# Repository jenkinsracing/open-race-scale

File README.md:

# open-race-scale
### Open Source Racecar Scale  
Four load cell scale controller for weighing cars using HX711 load cell module and Raspberry Pi platform. User interface will be via Bluetooth and smart phone app. The overall cost target goal for a complete car weighing system is under $230, at least 75% cheaper than commerically available car scales.
  
### Roadmap  
* Prototype electrical design as Raspberry Pi 3 Hat -> in progress  
* Create simple mechanical design for load cells -> in progress  
* Create Android/iOS app that will connect to the Rasberry Pi 3 to reccive live scale data (via bluetooth)  
* Add advanced features for storing weights for comparision  
* Add option of LCD screen directly on the Raspberry Pi 3  
* Get feedback and feature requests  
  
### Design

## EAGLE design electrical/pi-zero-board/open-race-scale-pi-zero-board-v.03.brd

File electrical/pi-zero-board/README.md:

### Open Race Scale Pi Zero based control board

***THIS BOARD IS NOT YET VALIDATED***

This is an early release version of the integrated control board.  It is not yet ready for production.  It has passed Eagle ERC and DRC for Seeed Fusion PCB.

Forked from https://github.com/jenkinsracing/open-race-scale by Andrew Jenkins no license listed

Uses Pi Zero and integrated HX711 amps instead of Pi 3 and HX711 carrier
boards.

HX711 circuit from Sparkfun Load Cell Amplifier https://github.com/sparkfun/HX711-Load-Cell-Amplifier/tree/V_1.1 license public domain/OSHW

Original designs from Roaddog Labs Ltd are released per the Open Source
Hardware Association guidelines for open source hardware at
http://www.oshwa.org/definition/.

Material specific to the components and documentation that is not
derived from other sources are released under the Creative Commons
Attribution 4.0 International license.

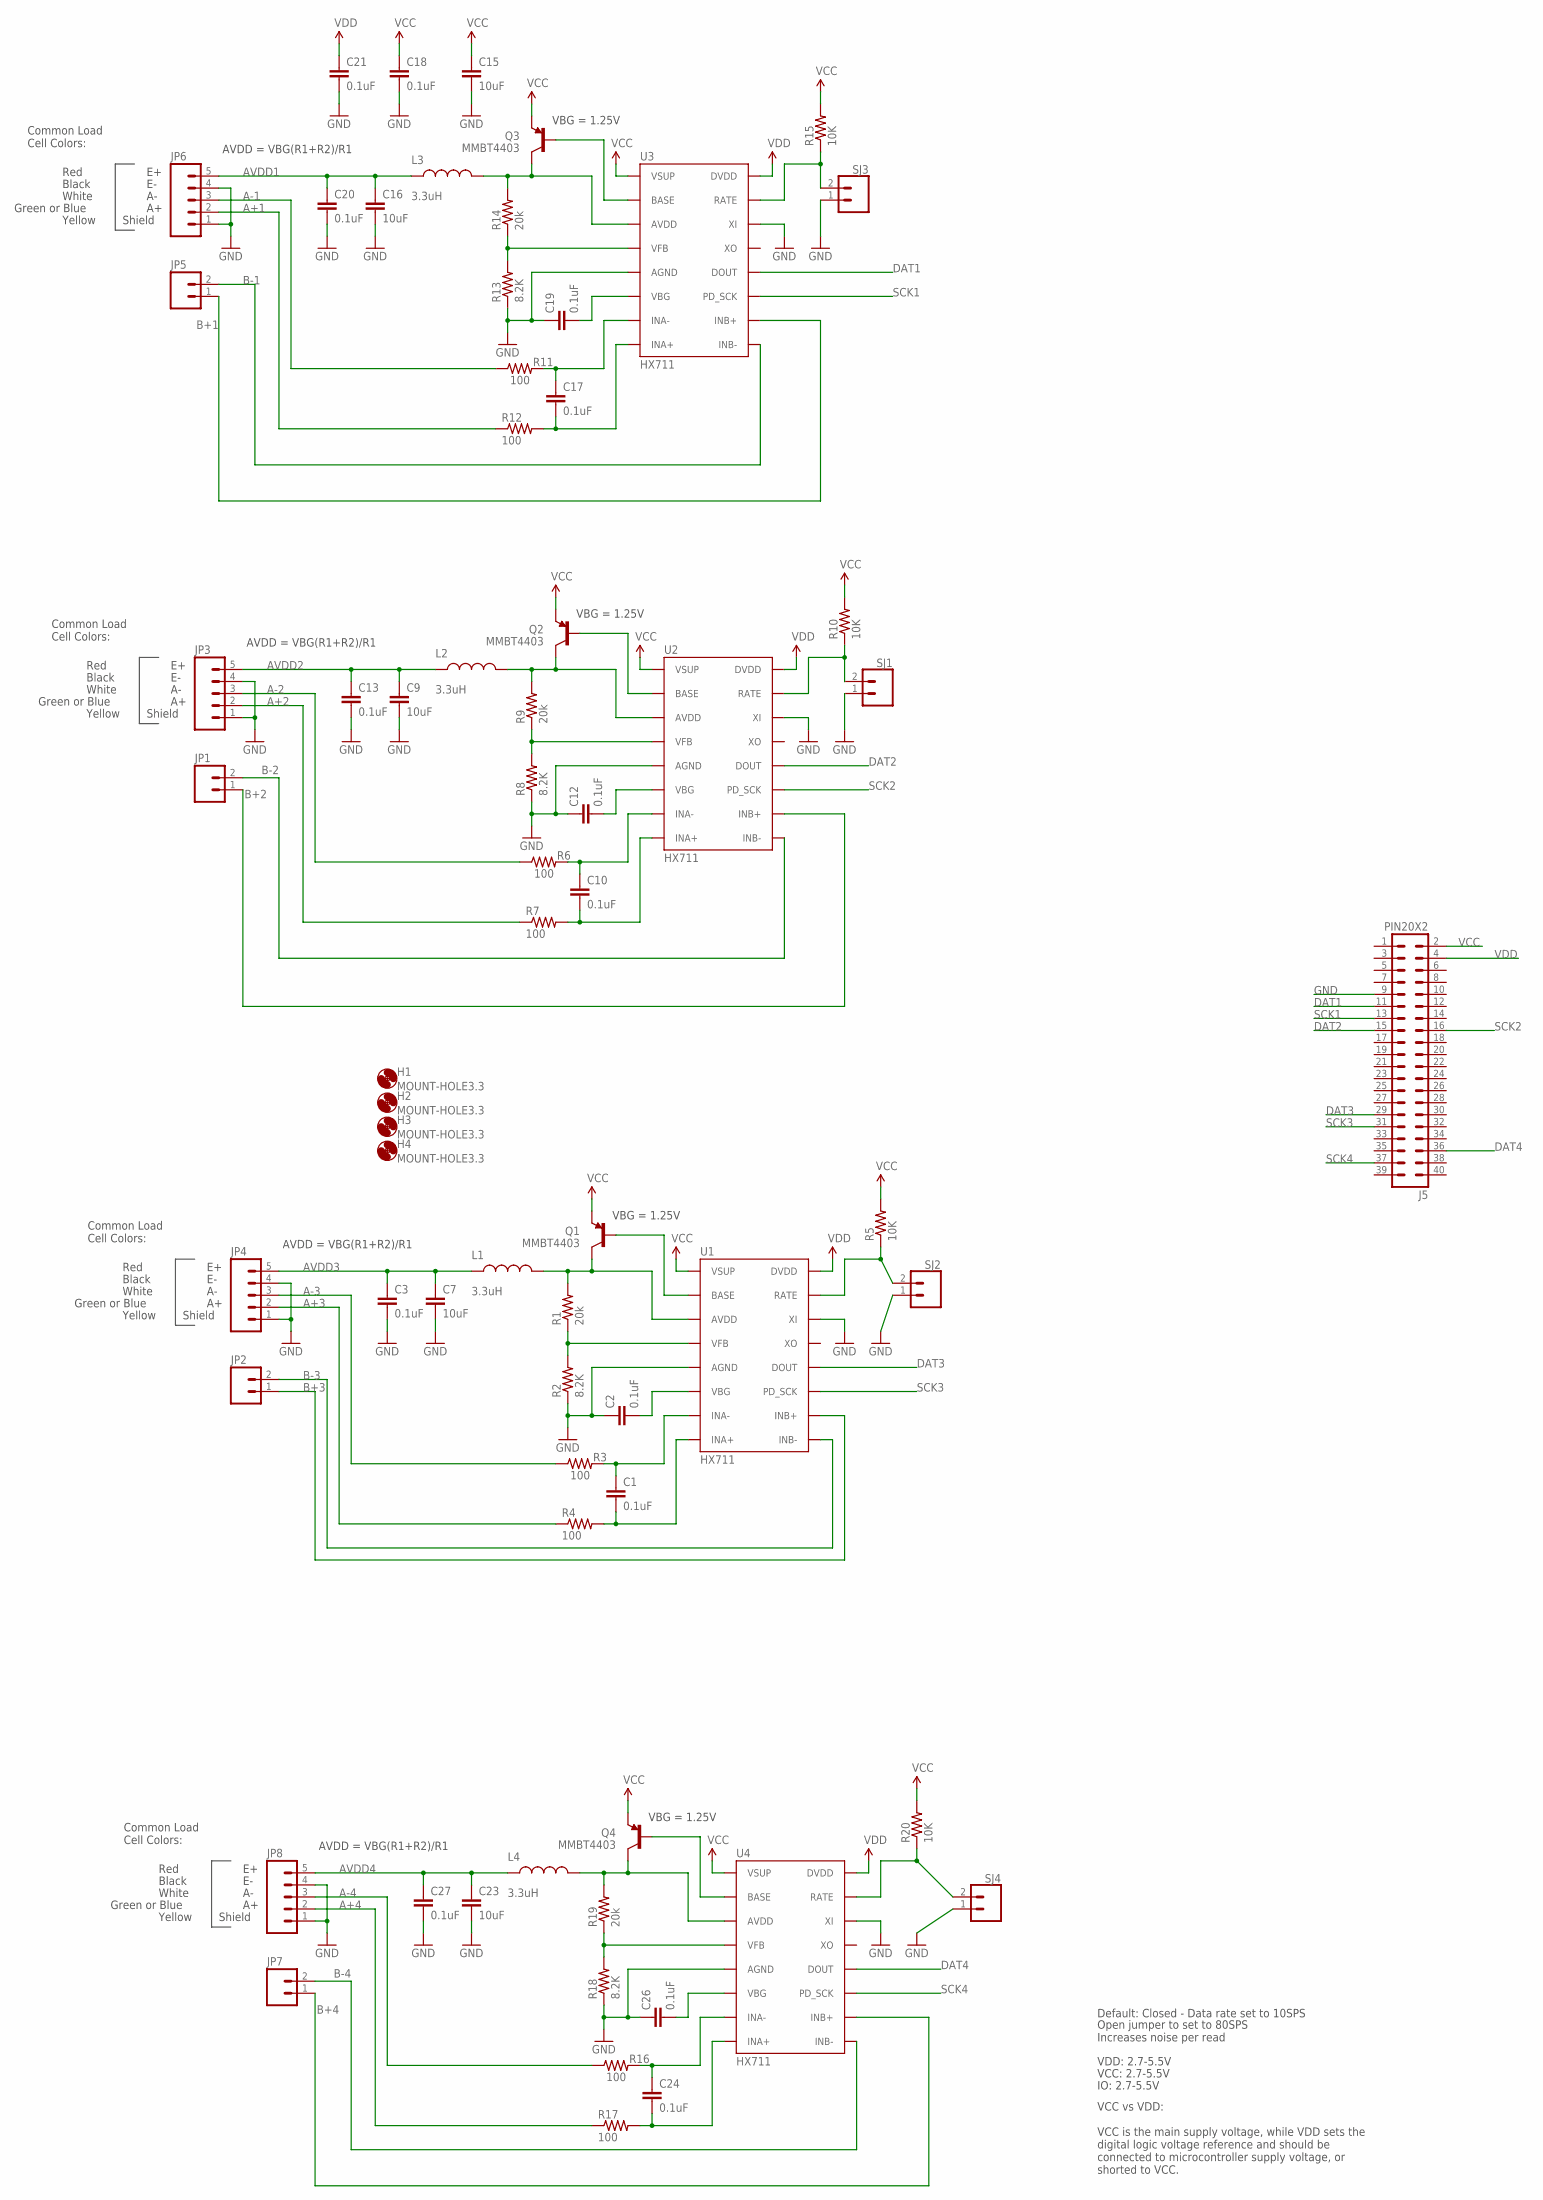
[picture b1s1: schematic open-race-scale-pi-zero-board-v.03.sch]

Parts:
C1, C2, C3, C10, C12, C13, C17, C18, C19, C20, C21, C24, C26, C27: 0.1uF; 0603-CAP
C7, C9, C15, C16, C23: 10uF; 1210
H1, H2, H3, H4: MOUNT-HOLE3.3; 3,3
J5: PIN20X2; PIN_20X2
JP1, JP2, JP5, JP7: M02PTH; 1X02@1
JP3, JP4, JP6, JP8: M05PTH; 1X05
L1, L2, L3, L4: 3.3uH; 0805
Q1, Q2, Q3, Q4: MMBT4403; SOT23-3
R1, R9, R14, R19: 20k; 0603-RES
R2, R8, R13, R18: 8.2K; 0603-RES
R3, R4, R6, R7, R11, R12, R16, R17: 100; 0603-RES
R5, R10, R15, R20: 10K; 0603-RES
SJ1, SJ2, SJ3, SJ4: CONN_02; 1X02
U1, U2, U3, U4: HX711; SO16

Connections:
A+1: JP6.2, R12.1
A+2: JP3.2, R7.1
A+3: JP4.2, R4.1
A+4: JP8.2, R17.1
A-1: JP6.3, R11.1
A-2: JP3.3, R6.1
A-3: JP4.3, R3.1
A-4: JP8.3, R16.1
AVDD1: C16.1, C20.1, JP6.5, L3.1
AVDD2: C9.1, C13.1, JP3.5, L2.1
AVDD3: C3.1, C7.1, JP4.5, L1.1
AVDD4: C23.1, C27.1, JP8.5, L4.1
B+1: JP5.1, U3.10 (INB+)
B+2: JP1.1, U2.10 (INB+)
B+3: JP2.1, U1.10 (INB+)
B+4: JP7.1, U4.10 (INB+)
B-1: JP5.2, U3.9 (INB-)
B-2: JP1.2, U2.9 (INB-)
B-3: JP2.2, U1.9 (INB-)
B-4: JP7.2, U4.9 (INB-)
DAT1: J5.11, U3.12 (DOUT)
DAT2: J5.15, U2.12 (DOUT)
DAT3: J5.29, U1.12 (DOUT)
DAT4: J5.36, U4.12 (DOUT)
GND: C2.1, C3.2, C7.2, C9.2, C12.1, C13.2, C15.2, C16.2, C18.2, C19.1, C20.2, C21.2, C23.2, C26.1, C27.2, J5.9, JP3.1, JP3.4, JP4.1, JP4.4, JP6.1, JP6.4, JP8.1, JP8.4, R2.1, R8.1, R13.1, R18.1, SJ1.1, SJ2.1, SJ3.1, SJ4.1, U1.5 (AGND), U1.14 (XI), U2.5 (AGND), U2.14 (XI), U3.5 (AGND), U3.14 (XI), U4.5 (AGND), U4.14 (XI)
unnamed: R5.1, SJ2.2, U1.15 (RATE)
unnamed: C1.1, R3.2, U1.7 (INA-)
unnamed: C1.2, R4.2, U1.8 (INA+)
unnamed: Q1.1 (B), U1.2 (BASE)
unnamed: L1.2, Q1.3 (C), R1.2, U1.3 (AVDD)
unnamed: R1.1, R2.2, U1.4 (VFB)
unnamed: C2.2, U1.6 (VBG)
unnamed: R8.2, R9.1, U2.4 (VFB)
unnamed: C12.2, U2.6 (VBG)
unnamed: C17.1, R11.2, U3.7 (INA-)
unnamed: C17.2, R12.2, U3.8 (INA+)
unnamed: Q4.1 (B), U4.2 (BASE)
unnamed: R18.2, R19.1, U4.4 (VFB)
unnamed: C26.2, U4.6 (VBG)
unnamed: L4.2, Q4.3 (C), R19.2, U4.3 (AVDD)
unnamed: R20.1, SJ4.2, U4.15 (RATE)
unnamed: C24.1, R16.2, U4.7 (INA-)
unnamed: C24.2, R17.2, U4.8 (INA+)
unnamed: Q2.1 (B), U2.2 (BASE)
unnamed: L2.2, Q2.3 (C), R9.2, U2.3 (AVDD)
unnamed: R10.1, SJ1.2, U2.15 (RATE)
unnamed: C10.1, R6.2, U2.7 (INA-)
unnamed: C10.2, R7.2, U2.8 (INA+)
unnamed: Q3.1 (B), U3.2 (BASE)
unnamed: R13.2, R14.1, U3.4 (VFB)
unnamed: C19.2, U3.6 (VBG)
unnamed: L3.2, Q3.3 (C), R14.2, U3.3 (AVDD)
unnamed: R15.1, SJ3.2, U3.15 (RATE)
SCK1: J5.13, U3.11 (PD_SCK)
SCK2: J5.16, U2.11 (PD_SCK)
SCK3: J5.31, U1.11 (PD_SCK)
SCK4: J5.37, U4.11 (PD_SCK)
VCC: C15.1, C18.1, J5.2, Q1.2 (E), Q2.2 (E), Q3.2 (E), Q4.2 (E), R5.2, R10.2, R15.2, R20.2, U1.1 (VSUP), U2.1 (VSUP), U3.1 (VSUP), U4.1 (VSUP)
VDD: C21.1, J5.4, U1.16 (DVDD), U2.16 (DVDD), U3.16 (DVDD), U4.16 (DVDD)

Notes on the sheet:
VBG = 1.25V
AVDD = VBG(R1+R2)/R1
Red
Black
White
Green or Blue
Common Load Cell Colors:
Shield
Yellow
VCC: 2.7-5.5V
Default: Closed - Data rate set to 10SPS
Open jumper to set to 80SPS Increases noise per read
IO: 2.7-5.5V
VDD: 2.7-5.5V
VCC vs VDD: VCC is the main supply voltage, while VDD sets the digital logic voltage reference and should be connected to microcontroller supply voltage, or shorted to VCC.

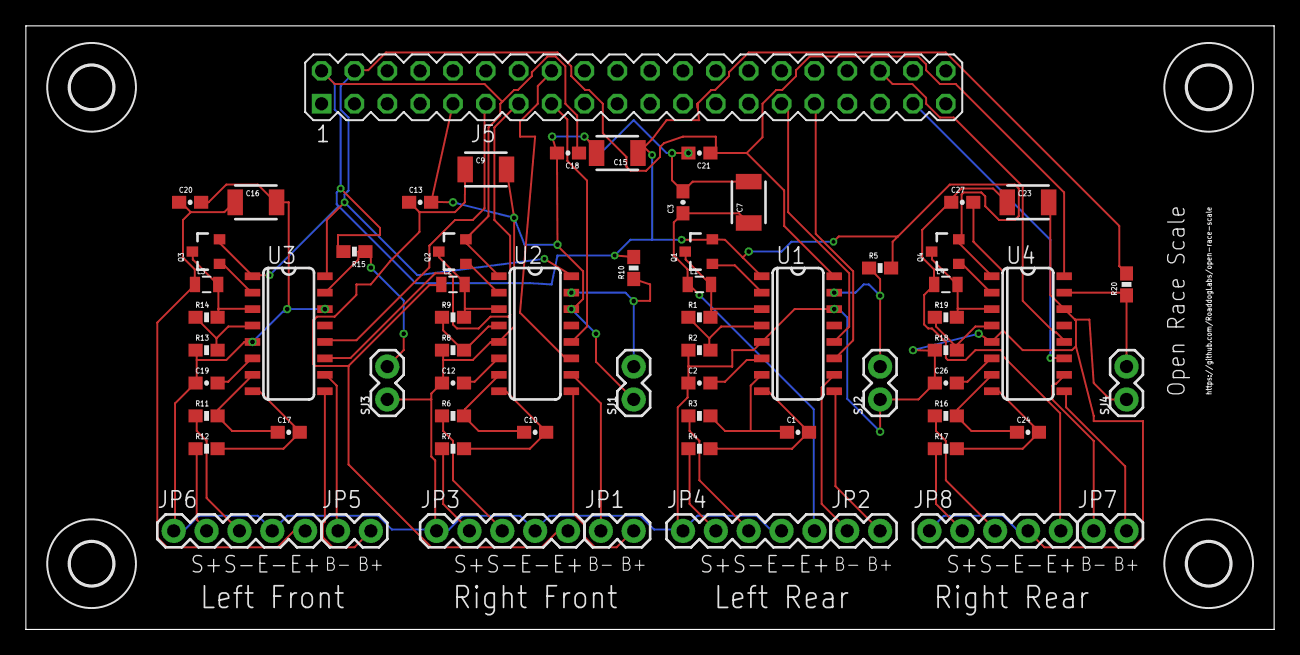
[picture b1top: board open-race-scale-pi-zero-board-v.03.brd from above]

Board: 2 copper layers, 96.5 x 46.7 mm, 68 parts (0 on the bottom side), 59 nets.

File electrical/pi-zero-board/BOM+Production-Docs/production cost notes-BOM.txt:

BOM for open race scale pi zero board with and without carriers

Partlist exported from /Users/dave/Documents/SparkFun_HX711_Load_Cell_v11/SparkFun_HX711_Load_Cell_v11.sch at 6/15/17 5:34 PM

Part      Value                      Device                     Package                           Description                          PROD_ID     VALUE   
4xC1        0.1uF                      0.1UF-25V-5%(0603)         0603-CAP                          CAP-08604                            CAP-08604   0.1uF   
4xC2        0.1uF                      0.1UF-25V-5%(0603)         0603-CAP                          CAP-08604                            CAP-08604   0.1uF   
4xC3        0.1uF                      0.1UF-25V-5%(0603)         0603-CAP                          CAP-08604                            CAP-08604   0.1uF   
4xC4        0.1uF                      0.1UF-25V-5%(0603)         0603-CAP                          CAP-08604                            CAP-08604   0.1uF   
4xC5        0.1uF                      0.1UF-25V-5%(0603)         0603-CAP                          CAP-08604                            CAP-08604   0.1uF   
4xC6        10uF                       10UF50V20%(1210)           1210                              CAP-09824                            CAP-09824   10uF    
4xC7        10uF                       10UF50V20%(1210)           1210                              CAP-09824                            CAP-09824   10uF    
4xJ1                                   M05PTH                     1X05                              Header 5                                                 
4xJP2                                  M02PTH                     1X02                              Standard 2-pin 0.1" header. Use with                     
4xJP4                                  M05PTH                     1X05                              Header 5                                                 
4xL1        3.3uH                      INDUCTOR0805-IND           0805                              Inductors                            NDUC-13076          
4xQ1        MMBT4403                   TRANSISTOR_PNPMMBT4403     SOT23-3                           Generic PNP BJT                      TRANS-09245 MMBT4403
4xR1        20k                        20KOHM1/10W1%(0603)        0603-RES                          RES-09383                            RES-09383   20k     
4xR2        8.2K                       8.2KOHM-1/10W-5%(0603)     0603-RES                          RES-10646                            RES-10646           
4xR3        100                        100OHM-1/10W-1%(0603)      0603-RES                          RES-07863                            RES-07863   100     
4xR4        100                        100OHM-1/10W-1%(0603)      0603-RES                          RES-07863                            RES-07863   100     
4xR5        10K                        10KOHM-1/10W-1%(0603)0603  0603-RES                          RES-00824                            RES-00824   10K     
SJ2                                  JUMPER-PAD-2-NC_BY_TRACE   PAD-JUMPER-2-NC_BY_TRACE_YES_SILK                                                          
                                                                                 
xxU1        HX711                      HX711HX711                 SO16                           Kynix http://www.kynix.com/Detail/627064/HX711.html                                        IC-12445    HX711   


Per the v1r2 board
parts kitted from Digikey for a single board (carriers) ors load cell amp #5313337 $11.03
HX711 @ .40 each from Kynix http://www.kynix.com/Detail/627064/HX711.html
pi gpio connector @1.50 ea from Adafruit  https://www.adafruit.com/product/2222 (pi zero needs 90* connector plus header pins)
4 x carrier board prototype @ .49 (panelized for 4 each per board) Seeed
1 x main board 2 layer prototype @ .49 each  Seeed

1 x main board 4 layer  @ 4.90 each  Seeed (we can cut that down with higher qty and another vendor approx $2.50 in 100 ql1ty

plug terminals are the main pain point on pricing

produced carrier boards with main board ($43.29 name brand terminals), ($21.09 import brand terminals) ($19.84 pin headers) no fab, stencil cost or shipping  (source less expensive pluggable blocks)
produced main board with import carrier boards ($40.26 name brand terminals) ($18.06 import brand terminals) ($16.81 pin headers)  minimal through hole assembly

produced integrated main board in 4 layer approx ($50 name brand terminals) ($27 import brand terminals) ($24 pin headers) no fab, stencil cost or shipping

pi zero w @10 Adafruit
pi 3 @39.95 Adafruit

pcba quotes

carriers
seeed  US$374.00 plus shipping for 100 carriers per sparkfun spec not panelized (not confirmed, no cost for hx711 and C5,C6, perhaps US$100 more)
bitelle/7pcb  US$642.27 plus shipping  for 100 carriers per sparkfun spec not panelized (not confirmed, no cost for hx711 yet)

integrated board
seeed need to finish gerber for quote
bitelle/7pcb  estimate US$ 452.76 plus shipping for 10 prototype no connectors and cost TBA on hx711.  Add US$200 for production quality.


bitelle/7pcb  estimate US$ 350.00 plus shipping for 5 prototype no connectors and cost TBA on hx711.

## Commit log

2017-05-30 Initial scale code
2017-05-31 Add schematics for V1
    Fritzing schematics for reading 4 load cells into RPi 3
2017-05-31 Improve schematic, add PCB
2017-06-01 Reorganize, Remake Fritzing
2017-06-01 Add gerber files for pcb
2017-06-01 Fix bread board img type
2017-06-01 Change to improved HX711 driver
    better bit handling
2017-06-01 Update LoadCell class
    Improved LC class with averaging to remove spikes
2017-06-01 Move LoadCell class
2017-06-06 Bluetooth base
2017-06-06 Organization
2017-06-06 Begin basic UI work
2017-06-07 Proof of concept reusable GUI
2017-06-07 Prepare core for GUI interactions
2017-06-07 Add screenshot
2017-06-07 Prepare bluetooth organization
    make a base class that will be subclassed based on platform
2017-06-07 Wrap bluetooth server into a class
2017-06-07 Improve ScaleControl
    start implementing calculations and data management
2017-06-07 Bluetooth work in app
2017-06-07 Add weight calculations, format text
2017-06-07 Set pins to match electrical
2017-06-07 Minor fix for ref unit
2017-06-07 Improve GUI
2017-06-15 add rs format gerbers
    add rs format berbers exported from Fritzing
    moved pdfs of gerbers to folder within gerber folder
2017-06-15 consolidate gerber folders
2017-06-15 add zip of berbers
2017-06-19 Rev 02 of PCB
    Remove redundant power pins, add jumper pins for selecting HX711 channel
2017-06-20 create fritzing part for XFW-HX711
    create custom fritzing part which matches the HX711 available on Amazon
2017-06-21 Update REV 02 with Chenbo HX711
    PCB now has HX711 mounting pads sized for the Chenbo HX711 pcb available
    from Amazon
2017-06-22 merge from jenkins
    merger latest fritzing board
2017-06-22 initial commit of pi zero branch
2017-06-22 initial commit schematic
2017-06-25 first cost draft
    includes both producing carriers and integrated board
2017-06-25 update for terminal options
    added import terminal and pin header cost models
2017-06-26 update pcbs costs and production BOMs
2017-06-26 update pcbs costs
2017-07-02 first rev of pi zero integrated board
    is compatible with all RPi, zero is used to control costs
2017-07-02 board passes etc and drc
2017-07-02 silk screen
2017-07-04 added ground trace
    upped rev number on ground trace add
2017-07-08 Fix widgets not updating
2017-07-08 Add standard app events for future, add logger
2017-07-08 Update screenshot
2017-07-08 Add hardware license

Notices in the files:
parts and their libraries:
SparkFun-Capacitors: Licensing: Creative Commons ShareAlike 4.0 International - https://creativecommons.org/licenses/by-sa/4.0
SparkFun-Connectors: Licensing: CC v3.0 Share-Alike You are welcome to use this library for commercial purposes.
